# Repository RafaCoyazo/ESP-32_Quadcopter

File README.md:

# ESP-32_Quadcopter

Purpose:
This repository documents a summer project dedicated to designing and building a custom quadcopter from scratch. At the core of the drone is a custom-designed PCB featuring an ESP32 microcontroller and an onboard accelerometer. While the final build has not yet achieved stable flight, the project served as an intensive, hands-on exploration of embedded C++, custom PCB routing, and writing raw PID control loops for hardware stabilization.

## Current Status & Known Issues

The physical build and custom PCB are complete, and the ESP32 successfully interfaces with the MPU6050 IMU and all four ESCs. However, the drone currently experiences a thrust imbalance where the rear motors do not reach the same RPM as the front motors, preventing a stable takeoff. 

**Troubleshooting to date:**

* Swapped the rear ESCs to rule out faulty hardware; the RPM deficit persisted.
* The isolated problem likely lies within the firmware's motor mixing logic, a bug in the PWM signal generation routed to the rear pins, or an uncompensated center of gravity on the 3D-printed frame.

## Hardware & Design

## Hardware Specifications

| Component | Description |
| :--- | :--- |
| **Microcontroller Evolution** | **V1 & V2:** Arduino (View [Version 1 Details](./Version_1) and [Version 2 Details](./Version_2))
|**Version 3**| **V3 Details of the Hardware:** [Version 3 Details](./Version_3)
  
* **Flight Controller:**
  * **Version 1:** Initial proof-of-concept testing was done using an Arduino and jumper wires.
  *  **Version 2:** Upgraded to a custom double-layer PCB (View the [KiCad Project Files](./Version_3/KiCadV3)) to show proof of concept with Arduino Nano
  * **Version 3:** Redigned custom double-layer PCB (View the [KiCad Project Files](./Version_3/KiCadV3)) to integrate the ESP32 and peripherals, wiring and reduce electrical noise.
 * **Schematic Design for V3**
*(Below: The wiring schematic integrating the ESP32 microcontroller, MPU6050 IMU, and peripheral modules.)*

**Frame Design & Manufacturing** 
*(Below: The original CAD model showcasing the structural assembly, followed by the final 3D-printed physical frame.)*

rplace with image]

## Software 

* **Language & Codebase Evolution:**
  * **V1 & V2:** Arduino / C++ (View [Version 1 Code](./Version_1) and [Version 2 Code](./Version_2)).
  * **V3:** Embedded C++ (View [Version 3 Code](./Version_3/CodeV3)).
* **Flight Logic:** Custom-written PID control loops to process IMU data and calculate real-time motor compensation.
* **Communication:** I2C protocol for reading sensor telemetry and PWM signal generation for the ESCs.

## Project Media
*(Note to self: Upload a photo of the completed drone and video)*

## Takeoff Dynamics & Motor Imbalance Diagnostics

During takeoff testing, the aircraft experienced a severe pitch imbalance where the rear motors visibly and physically generated significantly lower RPM and thrust compared to the front motors, preventing vertical liftoff.

### Diagnosed Causes & Experimental Troubleshooting:

1. **Power Supply & Input Voltage Verification:**
   * **Action:** Measured the primary voltage supply lines under load to check for power starvation or voltage drops to the rear power distribution traces.
   * **Result:** Confirmed that the power supply unit consistently delivers 12V across all board rails and ESC power feeds. Power delivery was ruled out as the root cause.

2. **ESC Timing, Calibration & Hardware Swaps:**
   * **Hypothesis:** Because four individual ESCs are used rather than an integrated 4-in-1 board, timing drift or throttle calibration offsets could cause rotational speed discrepancies between channels.
   * **Action:** Replaced the rear Electronic Speed Controllers with brand-new units to test for hardware degradation and calibration drift.
   * **Result:** Installing new ESCs slightly increased the RPM of one rear motor, but the total thrust was still insufficient to equalize the outputs. This confirms that while minor ESC variances exist, the main bottleneck is not faulty ESC hardware.

3. **Firmware Pitch Control Loops & Sensor Isolation:**
   * **Action:** To test if the MPU6050 IMU feedback loop was falsely commanding lower duty cycles to the rear channels, firmware was modified to temporarily isolate and disable active pitch compensation.
   * **Result:** Testing is currently ongoing to evaluate raw PWM output signal scaling, timer channel allocations on the ESP32 pins, and pitch PID loop behavior.

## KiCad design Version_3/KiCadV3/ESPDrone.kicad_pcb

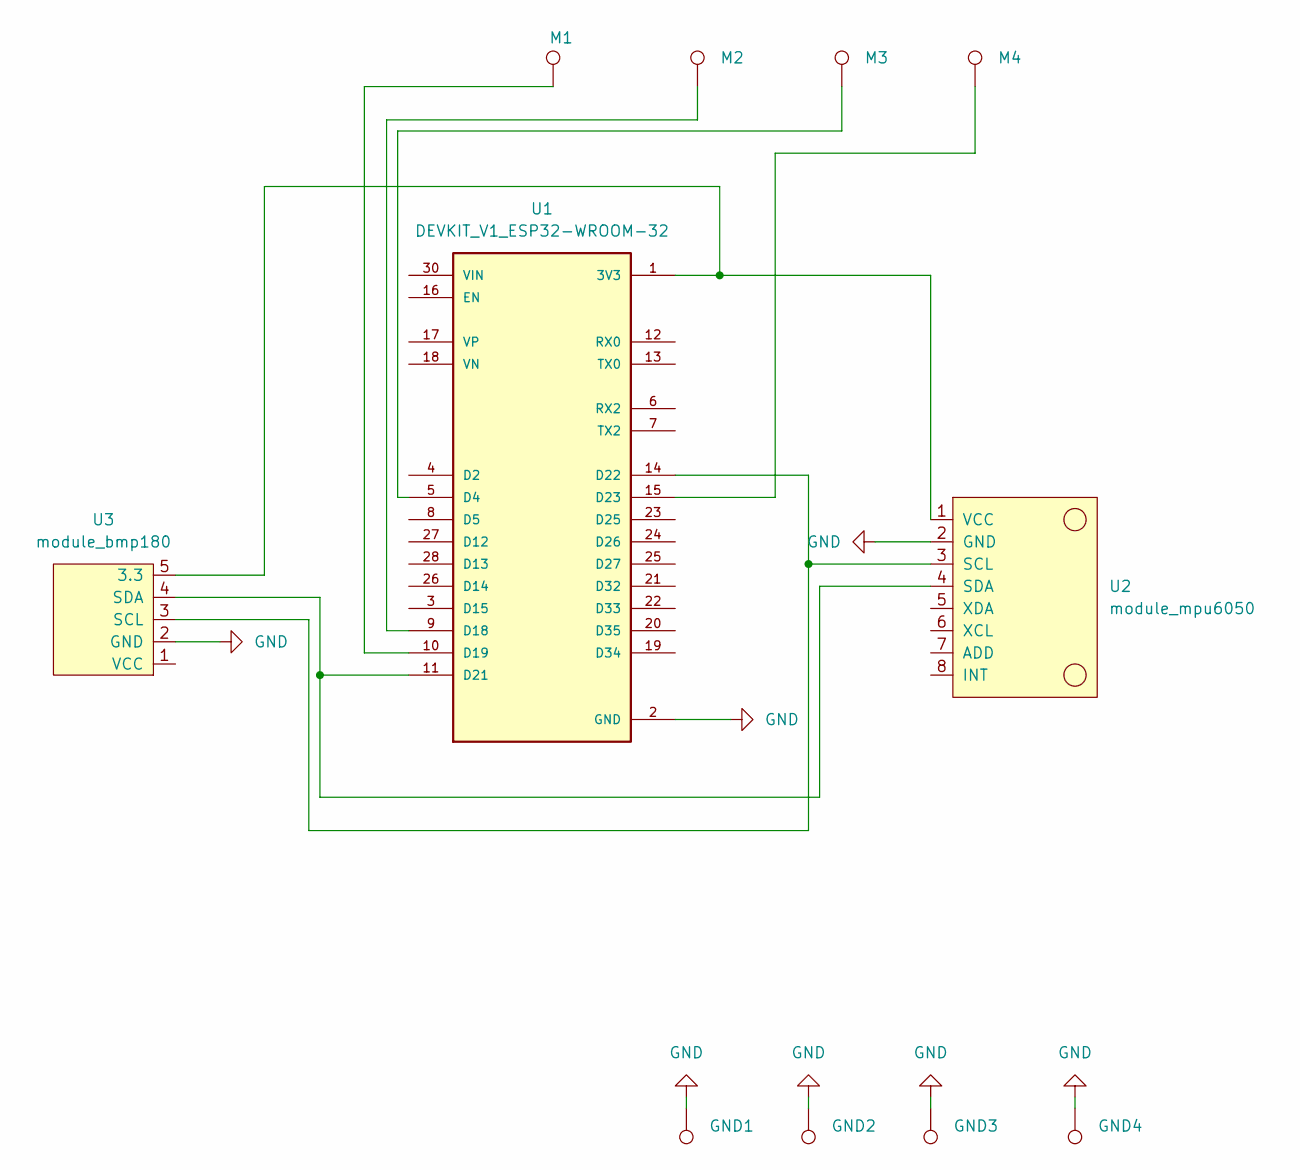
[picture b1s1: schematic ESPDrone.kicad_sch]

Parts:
GND1, GND2, GND3, GND4: TestPoint; TestPoint_THTPad_2.0x2.0mm_Drill1.0mm
M1: M1; TestPoint_THTPad_2.0x2.0mm_Drill1.0mm
M2, M3, M4: TestPoint; TestPoint_THTPad_2.0x2.0mm_Drill1.0mm
U1: DEVKIT_V1_ESP32-WROOM-32; MODULE_DEVKIT_V1_ESP32-WROOM-32
U2: module_mpu6050
U3: module_bmp180

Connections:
GND: GND1.1 (1_1), GND2.1 (1_1), GND3.1 (1_1), GND4.1 (1_1), U1.2 (GND), U1.29 (GND), U2.2 (GND), U3.2 (GND)
unnamed: U1.1 (3V3), U2.1 (VCC), U3.5 (3.3)
unnamed: M3.1 (1_1), U1.5 (D4)
unnamed: M2.1 (1_1), U1.9 (D18)
unnamed: M1.1 (1_1), U1.10 (D19)
unnamed: U1.11 (D21), U2.4 (SDA), U3.4 (SDA)
unnamed: U1.14 (D22), U2.3 (SCL), U3.3 (SCL)
unnamed: M4.1 (1_1), U1.15 (D23)

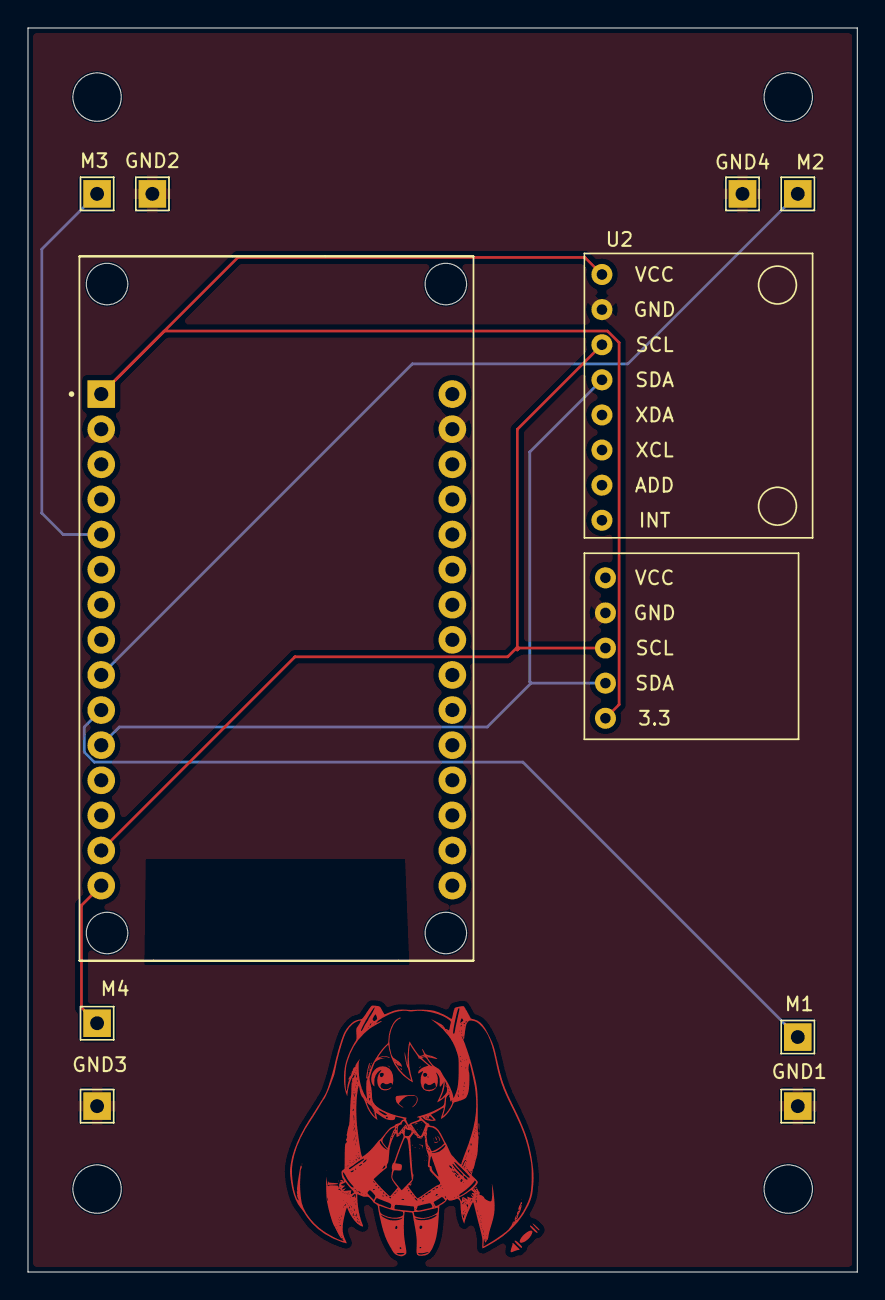
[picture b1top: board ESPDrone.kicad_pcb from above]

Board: 4 copper layers, 60.0 x 90.0 mm, 11 parts (0 on the bottom side), 8 nets.
